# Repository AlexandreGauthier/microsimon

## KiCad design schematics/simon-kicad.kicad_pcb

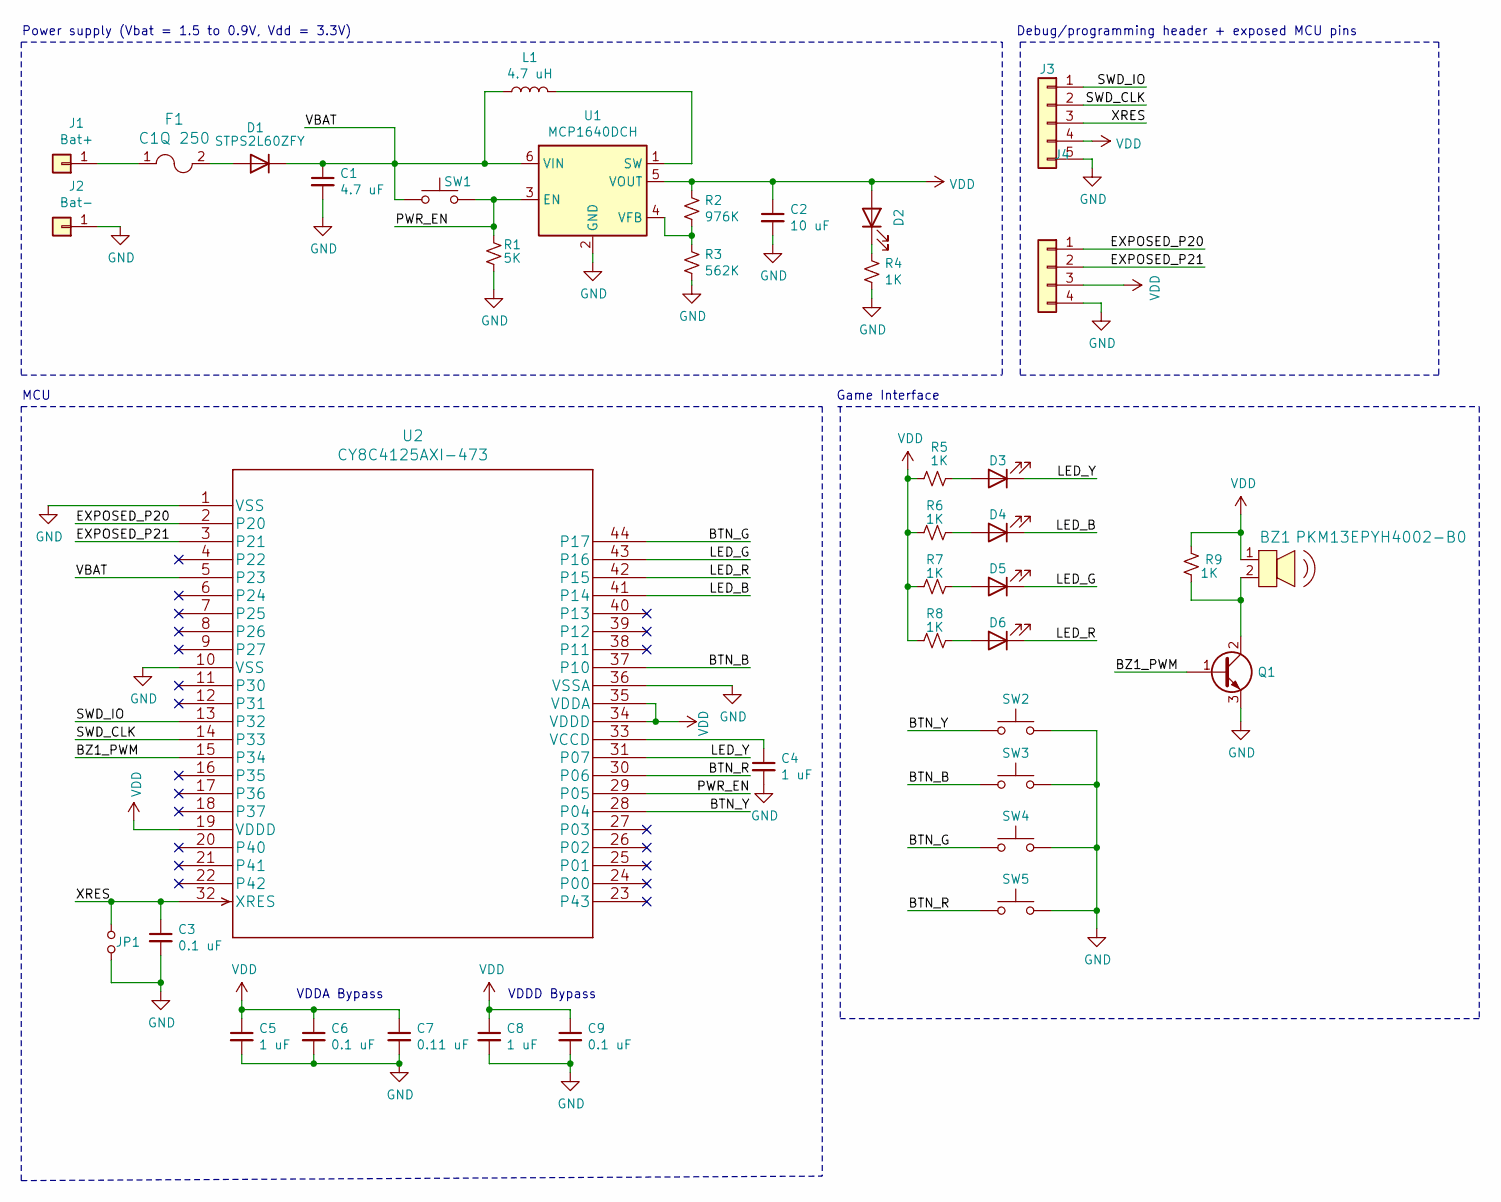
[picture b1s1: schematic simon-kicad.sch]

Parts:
BZ1: PKM13EPYH4002-B0; SPKR_PKM13EPYH4002-B0
C1: 4.7 uF; C_0805_2012Metric_Pad1.15x1.40mm_HandSolder
C2: 10 uF; C_0805_2012Metric_Pad1.15x1.40mm_HandSolder
C3, C6, C9: 0.1 uF; C_0603_1608Metric_Pad1.05x0.95mm_HandSolder
C4, C5, C8: 1 uF; C_0603_1608Metric_Pad1.05x0.95mm_HandSolder
C7: 0.11 uF; C_0603_1608Metric_Pad1.05x0.95mm_HandSolder
D1: ‎STPS2L60ZFY‎; D_SOD-123F
D2: ‎LNJ8W0C83RA‎; LED_0603_1608Metric_Pad1.05x0.95mm_HandSolder
D3, D4, D5, D6: LED; LED_0603_1608Metric_Pad1.05x0.95mm_HandSolder
F1: C1Q 250; Fuse_1206_3216Metric_Pad1.42x1.75mm_HandSolder
J1: Bat+; Keystone_597
J2: Bat-; Keystone_591_AAA
J3: SWD; PinHeader_1x05_P2.54mm_Vertical
J4: Not populated; 4_exposed_pins
JP1: RESET; SolderJumper-2_P1.3mm_Open_RoundedPad1.0x1.5mm
L1: 4.7 uH; L_0805_2012Metric_Pad1.15x1.40mm_HandSolder
Q1: ‎BC849B-TP‎; SOT-23
R1: 5K; R_0603_1608Metric_Pad1.05x0.95mm_HandSolder
R2: 976K; R_0603_1608Metric_Pad1.05x0.95mm_HandSolder
R3: 562K; R_0603_1608Metric_Pad1.05x0.95mm_HandSolder
R4, R5, R6, R7, R8, R9: 1K; R_0603_1608Metric_Pad1.05x0.95mm_HandSolder
SW1: SW_Push; El-cheapo red smd SPST
SW2, SW3, SW4, SW5: SW_Push; SW_Push_1P1T_NO_6x6mm_H9.5mm
U1: MCP1640DCH; SOT-23-6
U2: CY8C4125AXI-473; LQFP-44_10x10mm_P0.8mm

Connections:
/BTN_B: SW3.1, U2.37 (P10)
/BTN_G: SW4.1, U2.44 (P17)
/BTN_R: SW5.1, U2.30 (P06)
/BTN_Y: SW2.1, U2.28 (P04)
/BZ1_PWM: Q1.1 (B), U2.15 (P34)
/EXPOSED_P20: J4.1, U2.2 (P20)
/EXPOSED_P21: J4.2, U2.3 (P21)
/LED_B: D4.1 (K), U2.41 (P14)
/LED_G: D5.1 (K), U2.43 (P16)
/LED_R: D6.1 (K), U2.42 (P15)
/LED_Y: D3.1 (K), U2.31 (P07)
/PWR_EN: R1.1, SW1.2, U1.3 (EN), U2.29 (P05)
/SWD_CLK: J3.2, U2.14 (P33)
/SWD_IO: J3.1, U2.13 (P32)
/VBAT: C1.1, D1.1 (K), L1.1, SW1.1, U1.6 (VIN), U2.5 (P23)
/XRES: C3.1, J3.3, JP1.1, U2.32 (XRES)
GND: C1.2, C2.2, C3.2, C4.2, C5.2, C6.2, C7.2, C8.2, C9.2, J2.1, J3.5, J4.4, JP1.2, Q1.3 (E), R1.2, R3.2, R4.2, SW2.2, SW3.2, SW4.2, SW5.2, U1.2 (GND), U2.1 (VSS), U2.10 (VSS), U2.36 (VSSA)
unnamed: BZ1.2, Q1.2 (C), R9.1
unnamed: C4.1, U2.33 (VCCD)
unnamed: D1.2 (A), F1.2
unnamed: D2.1 (K), R4.1
unnamed: D3.2 (A), R5.1
unnamed: D4.2 (A), R6.1
unnamed: D5.2 (A), R7.1
unnamed: D6.2 (A), R8.1
unnamed: F1.1, J1.1
unnamed: L1.2, U1.1 (SW)
unnamed: R2.2, R3.1, U1.4 (VFB)
VDD: BZ1.1, C2.1, C5.1, C6.1, C7.1, C8.1, C9.1, D2.2 (A), J3.4, J4.3, R2.1, R5.2, R6.2, R7.2, R8.2, R9.2, U1.5 (VOUT), U2.19 (VDDD), U2.34 (VDDD), U2.35 (VDDA)

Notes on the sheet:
Power supply (Vbat = 1.5 to 0.9V, Vdd = 3.3V)
VDDA Bypass
VDDD Bypass
MCU
Game Interface
Debug/programming header + exposed MCU pins

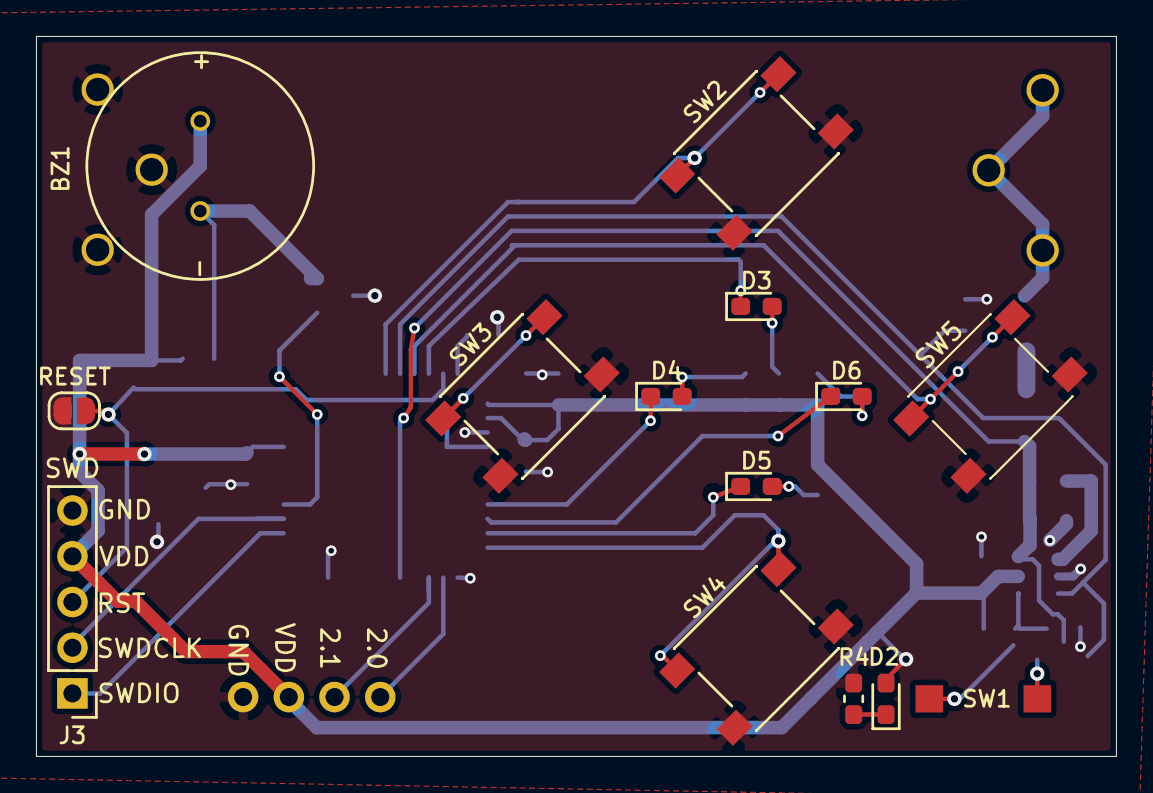
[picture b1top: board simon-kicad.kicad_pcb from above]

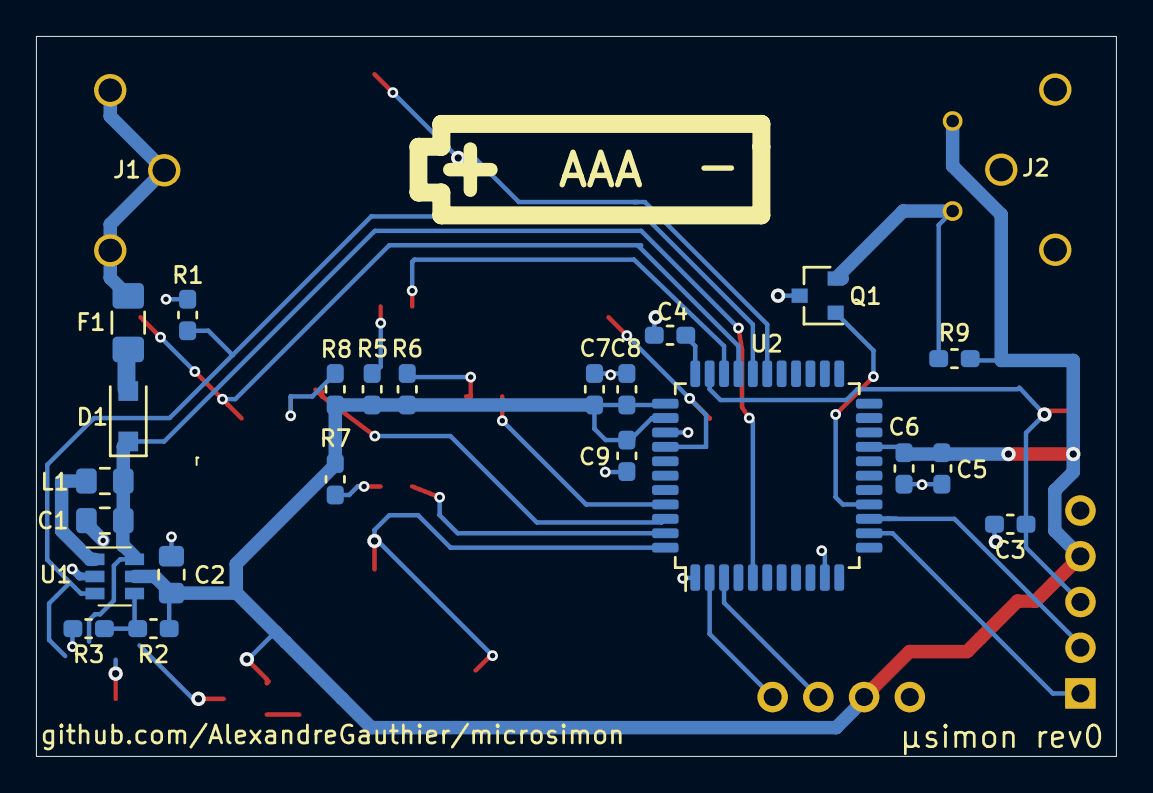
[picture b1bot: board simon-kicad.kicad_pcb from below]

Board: 2 copper layers, 60.0 x 40.0 mm, 40 parts (25 on the bottom side), 29 nets.

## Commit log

2020-10-18 layout rev0
2021-07-23 added firware to repo
2021-07-23 moved schematics pdf to root
